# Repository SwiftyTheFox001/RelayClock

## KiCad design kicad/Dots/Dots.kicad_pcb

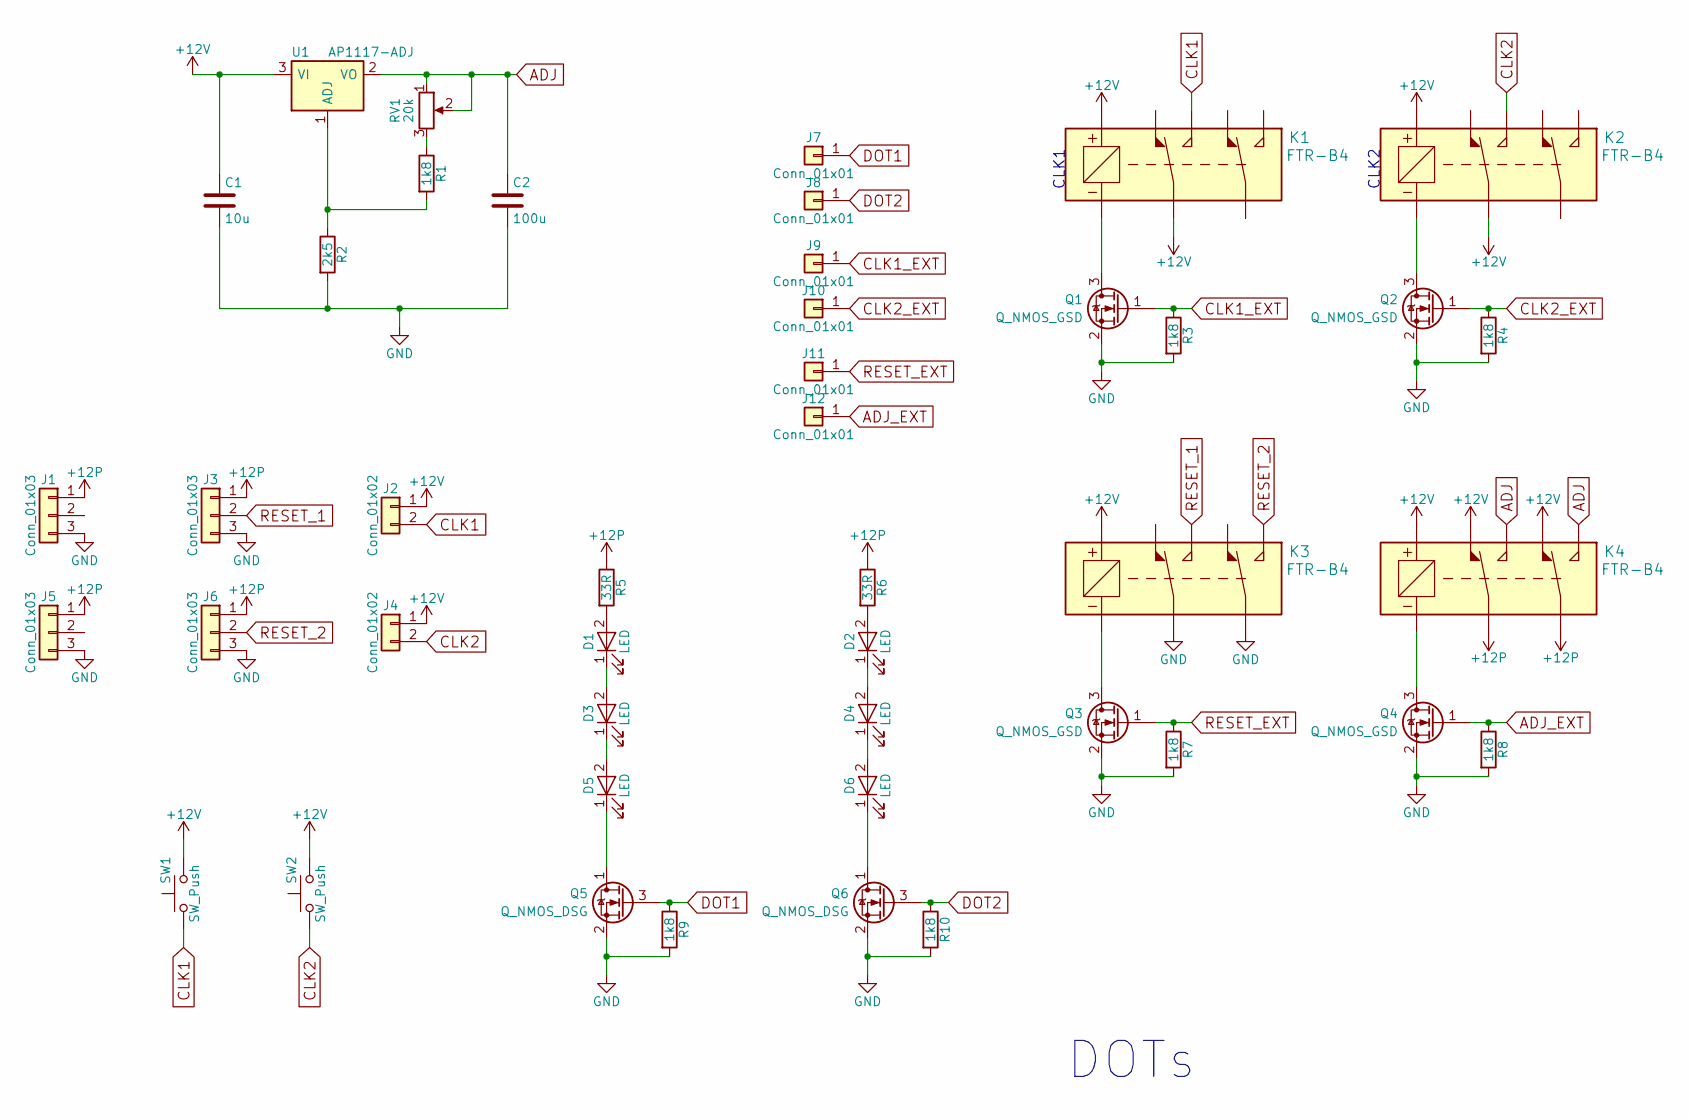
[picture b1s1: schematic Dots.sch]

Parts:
C1: 10u; C_Rect_L7.0mm_W3.5mm_P2.50mm_P5.00mm
C2: 100u; C_Rect_L7.0mm_W3.5mm_P2.50mm_P5.00mm
D1, D2, D3, D4, D5, D6: LED; LED_0805_2012Metric_Pad0.97x1.50mm_HandSolder
J1, J3, J5, J6: Conn_01x03; PinHeader_1x03_P2.54mm_Vertical
J2, J4: Conn_01x02; PinHeader_1x02_P2.54mm_Vertical
J7, J8, J9, J10, J11, J12: Conn_01x01; TestPoint_Pad_3.0x3.0mm
K1, K2, K3, K4: FTR-B4; FTR-B4_PTH
Q1, Q2, Q3, Q4: Q_NMOS_GSD; SOT-23
Q5, Q6: Q_NMOS_DSG; SOT-23
R1, R3, R4, R7, R8, R9, R10: 1k8; R_Axial_DIN0207_L6.3mm_D2.5mm_P10.16mm_Horizontal
R2: 2k5; R_Axial_DIN0207_L6.3mm_D2.5mm_P10.16mm_Horizontal
R5, R6: 33R; R_Axial_DIN0207_L6.3mm_D2.5mm_P10.16mm_Horizontal
RV1: 20k; TrimmPoti_Model23A_SMD
SW1, SW2: SW_Push; SW_PUSH_6mm
U1: AP1117-ADJ; SOT-223-3_TabPin2

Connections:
+12P: J1.1, J3.1, J5.1, J6.1, K4.3 (B2), K4.6 (A2), R5.1, R6.1
+12V: C1.1, J2.1, J4.1, K1.1 (+), K1.6 (A2), K2.1 (+), K2.6 (A2), K3.1 (+), K4.1 (+), K4.2 (B1), K4.7 (A1), SW1.2, SW2.2, U1.3 (VI)
ADJ: C2.1, K4.4 (B3), K4.5 (A3), RV1.1, RV1.2, U1.2 (VO)
ADJ_EXT: J12.1, Q4.1 (G), R8.1
CLK1: J2.2, K1.5 (A3), SW1.1
CLK1_EXT: J9.1, Q1.1 (G), R3.1
CLK2: J4.2, K2.5 (A3), SW2.1
CLK2_EXT: J10.1, Q2.1 (G), R4.1
DOT1: J7.1, Q5.3 (G), R9.1
DOT2: J8.1, Q6.3 (G), R10.1
GND: C1.2, C2.2, J1.3, J3.3, J5.3, J6.3, K3.3 (B2), K3.6 (A2), Q1.2 (S), Q2.2 (S), Q3.2 (S), Q4.2 (S), Q5.2 (S), Q6.2 (S), R2.2, R3.2, R4.2, R7.2, R8.2, R9.2, R10.2
unnamed: D1.1 (K), D3.2 (A)
unnamed: D1.2 (A), R5.2
unnamed: D2.1 (K), D4.2 (A)
unnamed: D2.2 (A), R6.2
unnamed: D3.1 (K), D5.2 (A)
unnamed: D4.1 (K), D6.2 (A)
unnamed: D5.1 (K), Q5.1 (D)
unnamed: D6.1 (K), Q6.1 (D)
unnamed: K1.8 (-), Q1.3 (D)
unnamed: K2.8 (-), Q2.3 (D)
unnamed: K3.8 (-), Q3.3 (D)
unnamed: K4.8 (-), Q4.3 (D)
unnamed: R1.1, RV1.3
unnamed: R1.2, R2.1, U1.1 (ADJ)
RESET_1: J3.2, K3.5 (A3)
RESET_2: J6.2, K3.4 (B3)
RESET_EXT: J11.1, Q3.1 (G), R7.1

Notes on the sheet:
CLK1
CLK2
DOTs

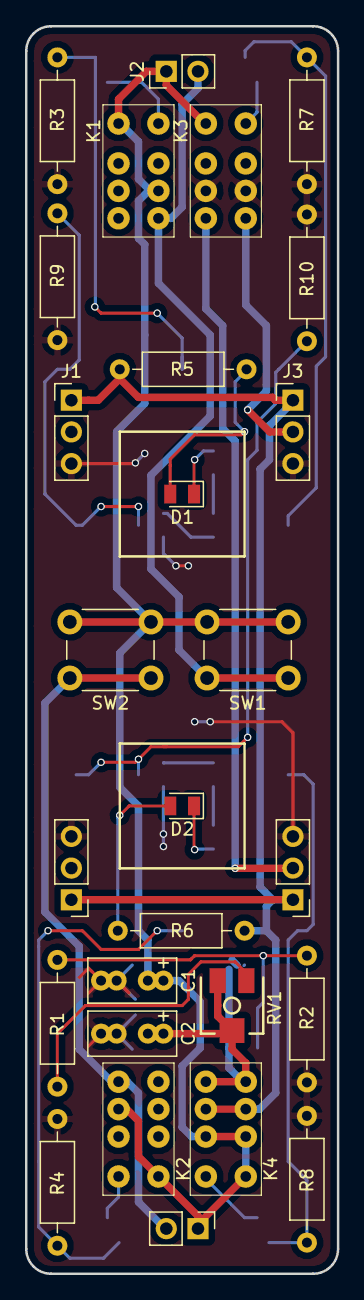
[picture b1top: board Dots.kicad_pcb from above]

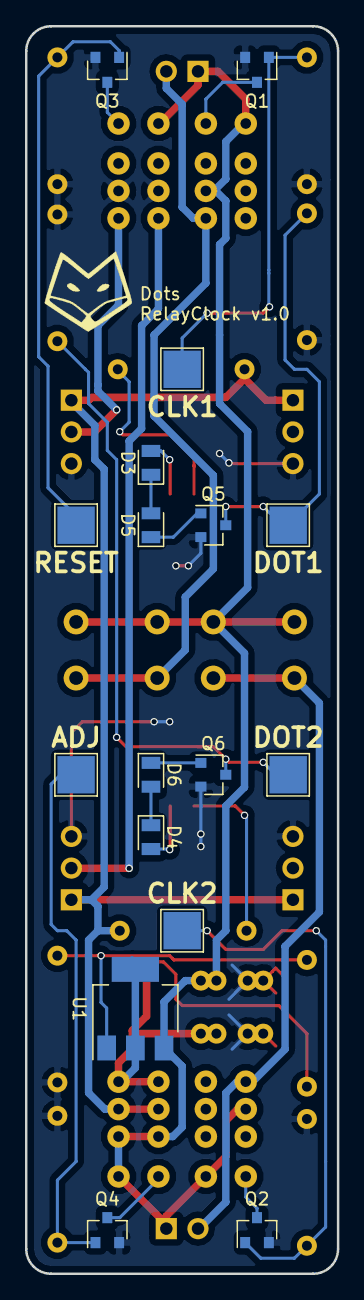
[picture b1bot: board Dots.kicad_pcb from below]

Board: 2 copper layers, 25.0 x 100.0 mm, 44 parts (17 on the bottom side), 28 nets.

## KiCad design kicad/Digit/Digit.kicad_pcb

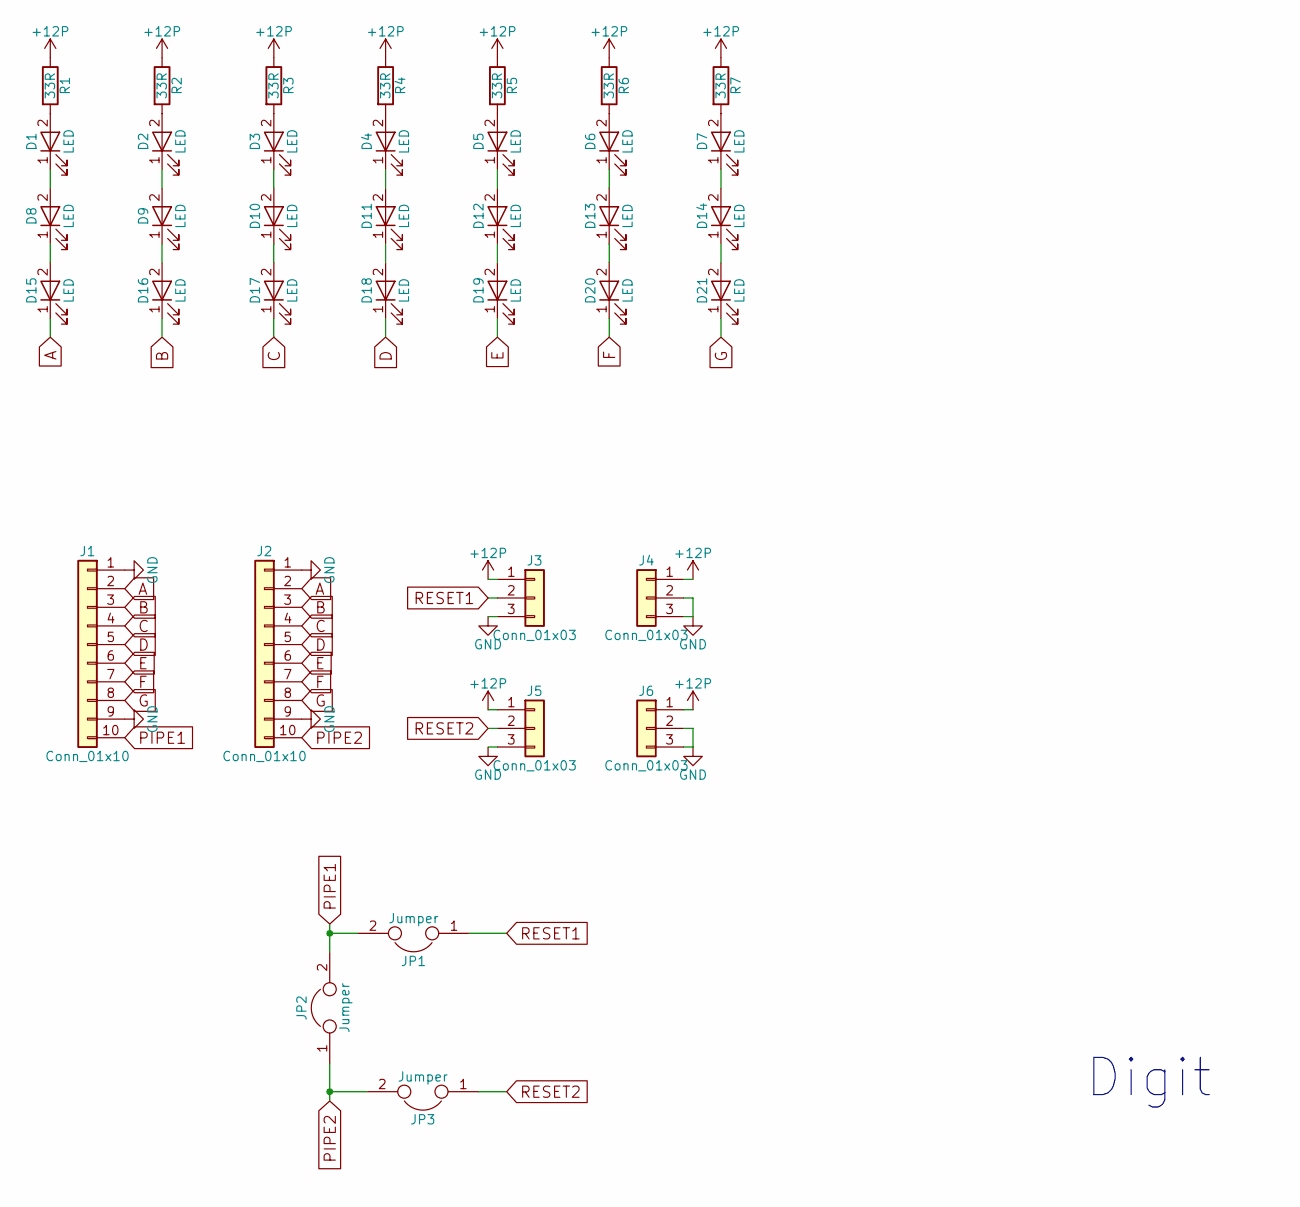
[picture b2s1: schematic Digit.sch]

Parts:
D1, D2, D3, D4, D5, D6, D7, D8, D9, D10, D11, D12, D13, D14, D15, D16, D17, D18, D19, D20, D21: LED; D_0805_2012Metric_Pad0.97x1.50mm_HandSolder
J1, J2: Conn_01x10; PinHeader_1x10_P2.54mm_Vertical
J3, J4, J5, J6: Conn_01x03; PinHeader_1x03_P2.54mm_Vertical
JP1, JP2, JP3: Jumper; SolderJumper_01x02
R1, R2, R3, R4, R5, R6, R7: 33R; R_Axial_DIN0207_L6.3mm_D2.5mm_P10.16mm_Horizontal

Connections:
+12P: J3.1, J4.1, J5.1, J6.1, R1.1, R2.1, R3.1, R4.1, R5.1, R6.1, R7.1
A: D15.1 (K), J1.2, J2.2
B: D16.1 (K), J1.3, J2.3
C: D17.1 (K), J1.4, J2.4
D: D18.1 (K), J1.5, J2.5
E: D19.1 (K), J1.6, J2.6
F: D20.1 (K), J1.7, J2.7
G: D21.1 (K), J1.8, J2.8
GND: J1.1, J1.9, J2.1, J2.9, J3.3, J4.2, J4.3, J5.3, J6.2, J6.3
unnamed: D1.1 (K), D8.2 (A)
unnamed: D1.2 (A), R1.2
unnamed: D2.1 (K), D9.2 (A)
unnamed: D2.2 (A), R2.2
unnamed: D3.2 (A), R3.2
unnamed: D4.2 (A), R4.2
unnamed: D5.2 (A), R5.2
unnamed: D6.2 (A), R6.2
unnamed: D7.2 (A), R7.2
unnamed: D10.1 (K), D17.2 (A)
unnamed: D3.1 (K), D10.2 (A)
unnamed: D11.1 (K), D18.2 (A)
unnamed: D4.1 (K), D11.2 (A)
unnamed: D12.1 (K), D19.2 (A)
unnamed: D5.1 (K), D12.2 (A)
unnamed: D13.1 (K), D20.2 (A)
unnamed: D6.1 (K), D13.2 (A)
unnamed: D14.1 (K), D21.2 (A)
unnamed: D7.1 (K), D14.2 (A)
unnamed: D8.1 (K), D15.2 (A)
unnamed: D9.1 (K), D16.2 (A)
PIPE1: J1.10, JP1.2, JP2.2
PIPE2: J2.10, JP2.1, JP3.2
RESET1: J3.2, JP1.1
RESET2: J5.2, JP3.1

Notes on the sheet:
Digit

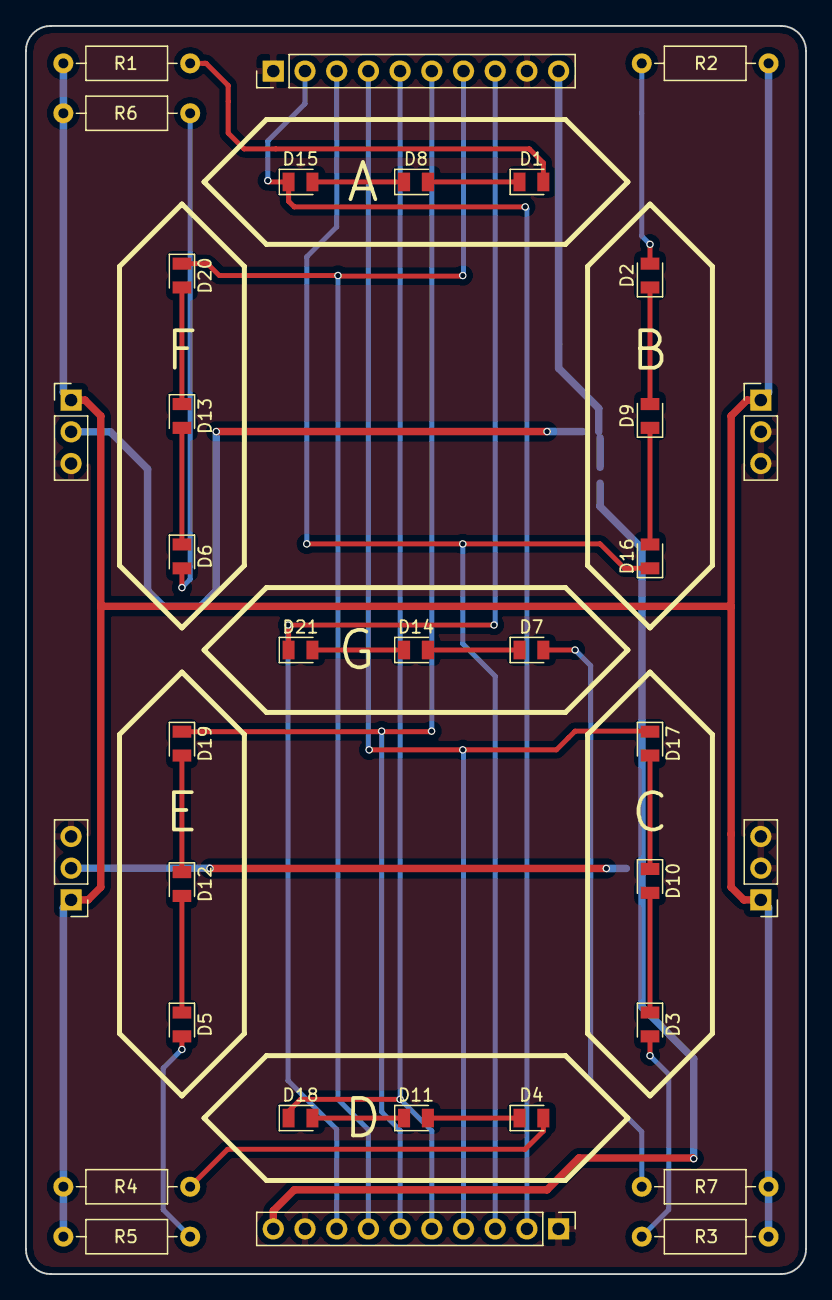
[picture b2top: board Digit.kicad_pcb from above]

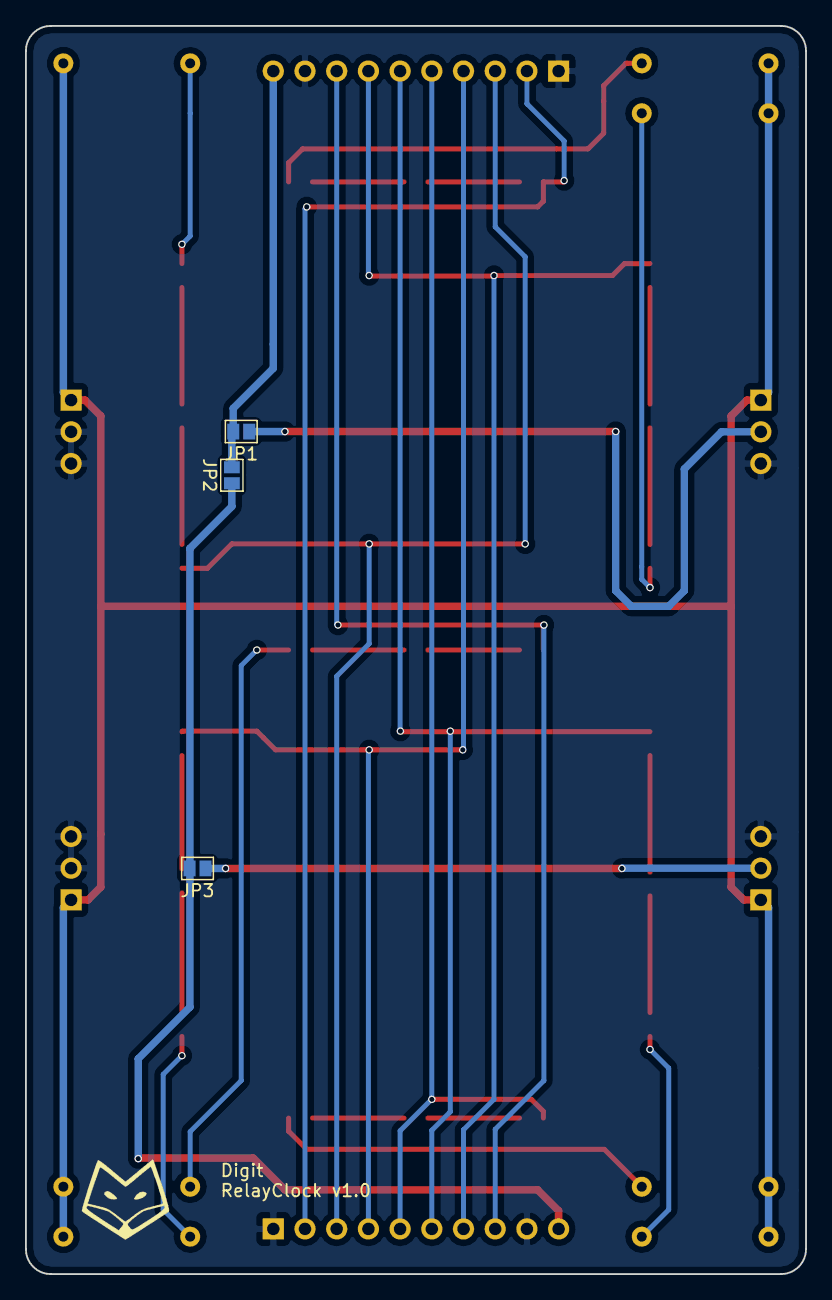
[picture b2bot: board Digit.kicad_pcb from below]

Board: 2 copper layers, 62.5 x 100.0 mm, 37 parts (3 on the bottom side), 34 nets.

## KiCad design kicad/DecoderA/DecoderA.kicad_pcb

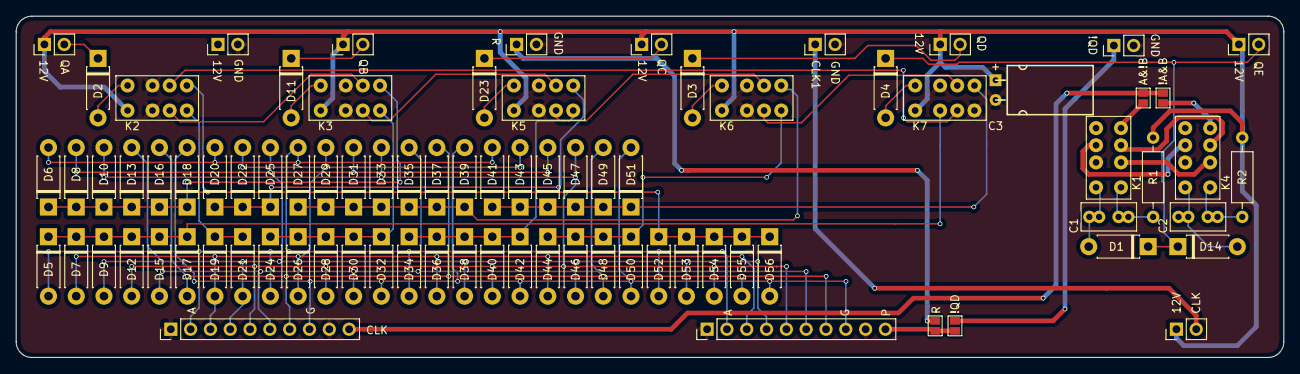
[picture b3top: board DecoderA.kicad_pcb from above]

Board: 2 copper layers, 162.5 x 43.8 mm, 84 parts (0 on the bottom side), 48 nets.

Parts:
C1, C2: CP; C_Rect_L7.0mm_W3.5mm_P2.50mm_P5.00mm
C3: CP; CP_Radial_D6.3mm_P2.50mm_W11.00mm_vertical
D1, D2, D3, D4, D5, D6, D7, D8, D9, D10, D11, D12, D13, D14, D15, D16, D17, D18, D19, D20, D21, D22, D23, D24, D25, D26, D27, D28, D29, D30, D31, D32, D33, D34, D35, D36, D37, D38, D39, D40, D41, D42, D43, D44, D45, D46, D47, D48, D49, D50, D51, D52, D53, D54, D55, D56: D; D_DO-41_SOD81_P7.62mm_Horizontal
J1, J2, J3, J4, J5, J6, J7, J10, J11, J12: Conn_01x02; PinHeader_1x02_P2.54mm_Vertical
J8, J9: Conn_01x10; PinHeader_1x10_P2.54mm_Vertical
JP1, JP2, JP3, JP4: Jumper; SolderJumper_01x02
K1, K2, K3, K4, K5, K6, K7: FTR-B4; FTR-B4_PTH
R1, R2: 100R; R_Axial_DIN0207_L6.3mm_D2.5mm_P10.16mm_Horizontal

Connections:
!A&B_POS: JP2.1, K4.4
!QD: J12.1, JP4.1
+12V: C3.1, J1.1, J2.1, J3.1, J4.1, J10.1, J11.1, K2.1, K3.1, K5.1, K6.1, K7.1, R1.1, R2.1
A: D5.2, D6.2, D20.2, D24.2, D27.2, D34.2, D41.2, D52.2, J8.2, J9.2
A&!B_POS: JP1.1, K1.4
B: D7.2, D19.2, D22.2, D26.2, D29.2, D36.2, D43.2, D44.2, J8.3, J9.3
C: D8.2, D9.2, D21.2, D25.2, D31.2, D38.2, D45.2, D46.2, D53.2, J8.4, J9.4
CLK1: J7.1, J11.2
CLK2: J9.10, JP1.2, JP2.2
D: D10.2, D12.2, D28.2, D33.2, D40.2, D47.2, D54.2, J8.5, J9.5
E: D13.2, D15.2, D30.2, D35.2, J8.6, J9.6
F: D16.2, D17.2, D37.2, D48.2, D49.2, D55.2, J8.7, J9.7
G: D18.2, D32.2, D39.2, D42.2, D50.2, D51.2, D56.2, J8.8, J9.8
GND: C3.2, J5.2, J6.2, J7.2, J8.1, J8.9, J9.1, J9.9, J12.2, K1.7, K2.2, K2.7, K3.2, K3.7, K4.7, K5.2, K5.7, K6.2, K6.7, K7.4, K7.7
NUM0: D5.1, D7.1, D9.1, D12.1, D15.1, D17.1, K7.2
NUM1: D19.1, D21.1, K2.4
NUM2: D24.1, D26.1, D28.1, D30.1, D32.1, K3.4
NUM3: D34.1, D36.1, D38.1, D40.1, D42.1, K5.4
NUM4: D44.1, D46.1, D48.1, D50.1, K6.4
NUM5: D52.1, D53.1, D54.1, D55.1, D56.1, K2.5
NUM6: D6.1, D8.1, D10.1, D13.1, D16.1, D18.1, K3.5
NUM7: D20.1, D22.1, D25.1, K5.5
NUM8: D27.1, D29.1, D31.1, D33.1, D35.1, D37.1, D39.1, K6.5
NUM9: D41.1, D43.1, D45.1, D47.1, D49.1, D51.1, K7.5
unnamed: C1.1, K1.1, R1.2
unnamed: C1.2, D1.2, K1.8
unnamed: C2.1, K4.1, R2.2
unnamed: C2.2, D14.2, K4.8
unnamed: D2.2, K2.8
unnamed: D3.2, K6.8
unnamed: D4.2, K7.8
unnamed: D11.2, K3.8
unnamed: D23.2, K5.8
unnamed: K1.2, K4.2
unnamed: K1.3, K4.3
unnamed: K1.6, K4.6
unnamed: K2.3, K3.6
unnamed: K2.6, K7.3
unnamed: K3.3, K5.6
unnamed: K5.3, K6.6
unnamed: K6.3, K7.6
PIPE: J8.10, JP3.2, JP4.2
QA: D2.1, J1.2
QB: D11.1, J2.2
QC: D23.1, J3.2
QD: D3.1, J4.2
QE: D1.1, D4.1, D14.1, J10.2
RESET: J6.1, JP3.1

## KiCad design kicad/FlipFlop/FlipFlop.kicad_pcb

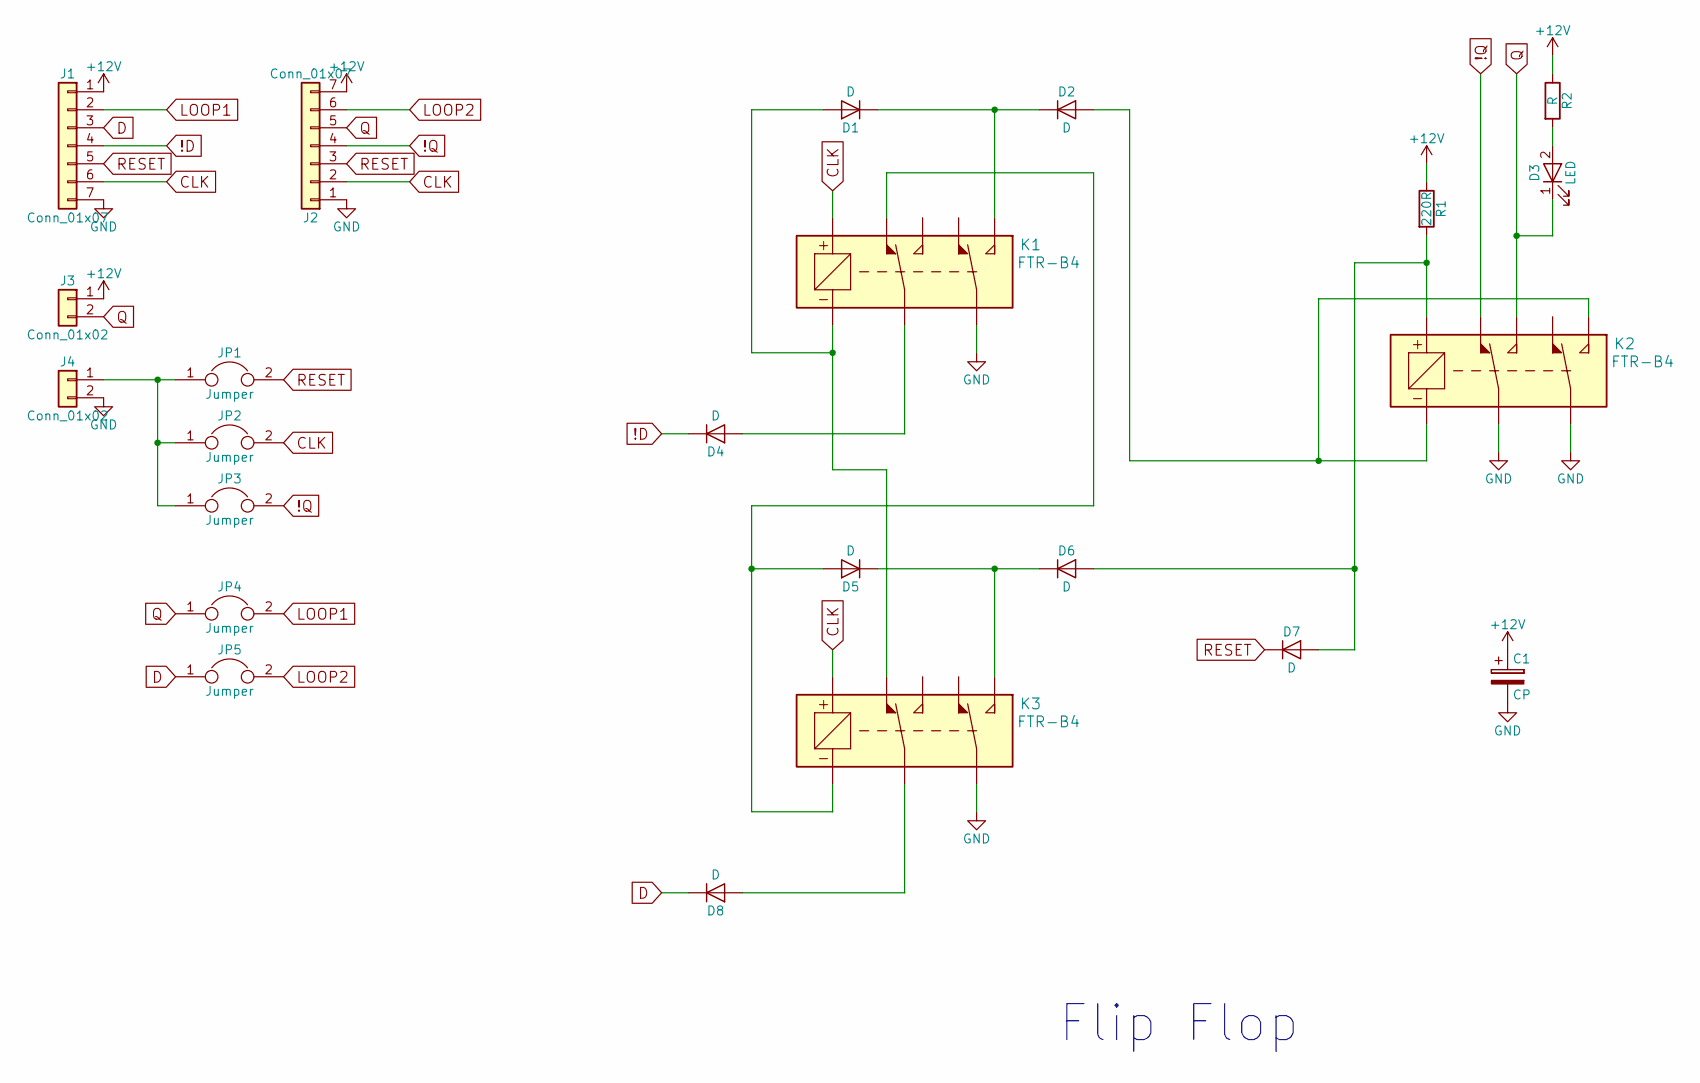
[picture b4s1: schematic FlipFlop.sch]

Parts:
C1: CP; CP_Radial_D6.3mm_P2.50mm_W11.00mm_vertical
D1, D2, D5, D6: D; D_DO-41_SOD81_P7.62mm_Horizontal
D3: LED; LED_0805_2012Metric_Pad0.97x1.50mm_HandSolder
D4, D7, D8: D; D_DO-41_SOD81_P2.54mm_Vertical_AnodeUp
J1, J2: Conn_01x07; PinHeader_1x07_P2.54mm_Vertical
J3, J4: Conn_01x02; PinHeader_1x02_P2.54mm_Vertical
JP1, JP2, JP3, JP4, JP5: Jumper; SolderJumper_01x02
K1, K2, K3: FTR-B4; FTR-B4_PTH
R1: 220R; R_Axial_DIN0207_L6.3mm_D2.5mm_P10.16mm_Horizontal
R2: R; R_Axial_DIN0207_L6.3mm_D2.5mm_P10.16mm_Horizontal

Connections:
!D: D4.1 (K), J1.4
!Q: J2.4, JP3.2, K2.7 (A1)
+12V: C1.1, J1.1, J2.7, J3.1, R1.1, R2.1
CLK: J1.6, J2.2, JP2.2, K1.1 (+), K3.1 (+)
D: D8.1 (K), J1.3, JP5.1
GND: C1.2, J1.7, J2.1, J4.2, K1.3 (B2), K2.3 (B2), K2.6 (A2), K3.3 (B2)
LOOP1: J1.2, JP4.2
LOOP2: J2.6, JP5.2
unnamed: D1.1 (K), D2.1 (K), K1.4 (B3)
unnamed: D1.2 (A), K1.8 (-), K3.7 (A1)
unnamed: D2.2 (A), K2.4 (B3), K2.8 (-)
unnamed: D3.2 (A), R2.2
unnamed: D4.2 (A), K1.6 (A2)
unnamed: D5.1 (K), D6.1 (K), K3.4 (B3)
unnamed: D5.2 (A), K1.7 (A1), K3.8 (-)
unnamed: D6.2 (A), D7.2 (A), K2.1 (+), R1.2
unnamed: D8.2 (A), K3.6 (A2)
unnamed: J4.1, JP1.1, JP2.1, JP3.1
Q: D3.1 (K), J2.5, J3.2, JP4.1, K2.5 (A3)
RESET: D7.1 (K), J1.5, J2.3, JP1.2

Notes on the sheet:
Flip Flop

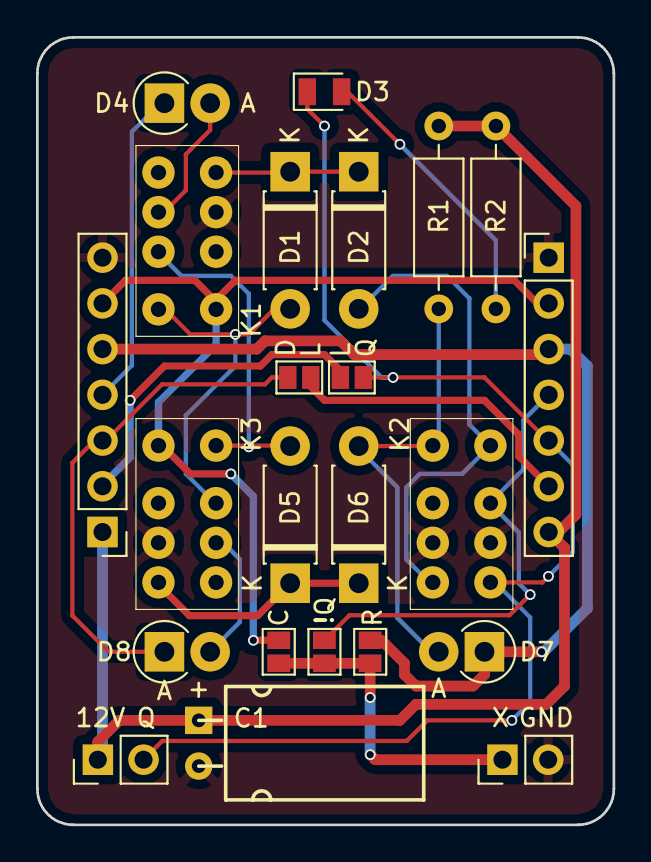
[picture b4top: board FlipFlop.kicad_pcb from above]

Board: 2 copper layers, 32.0 x 43.8 mm, 23 parts (0 on the bottom side), 20 nets.

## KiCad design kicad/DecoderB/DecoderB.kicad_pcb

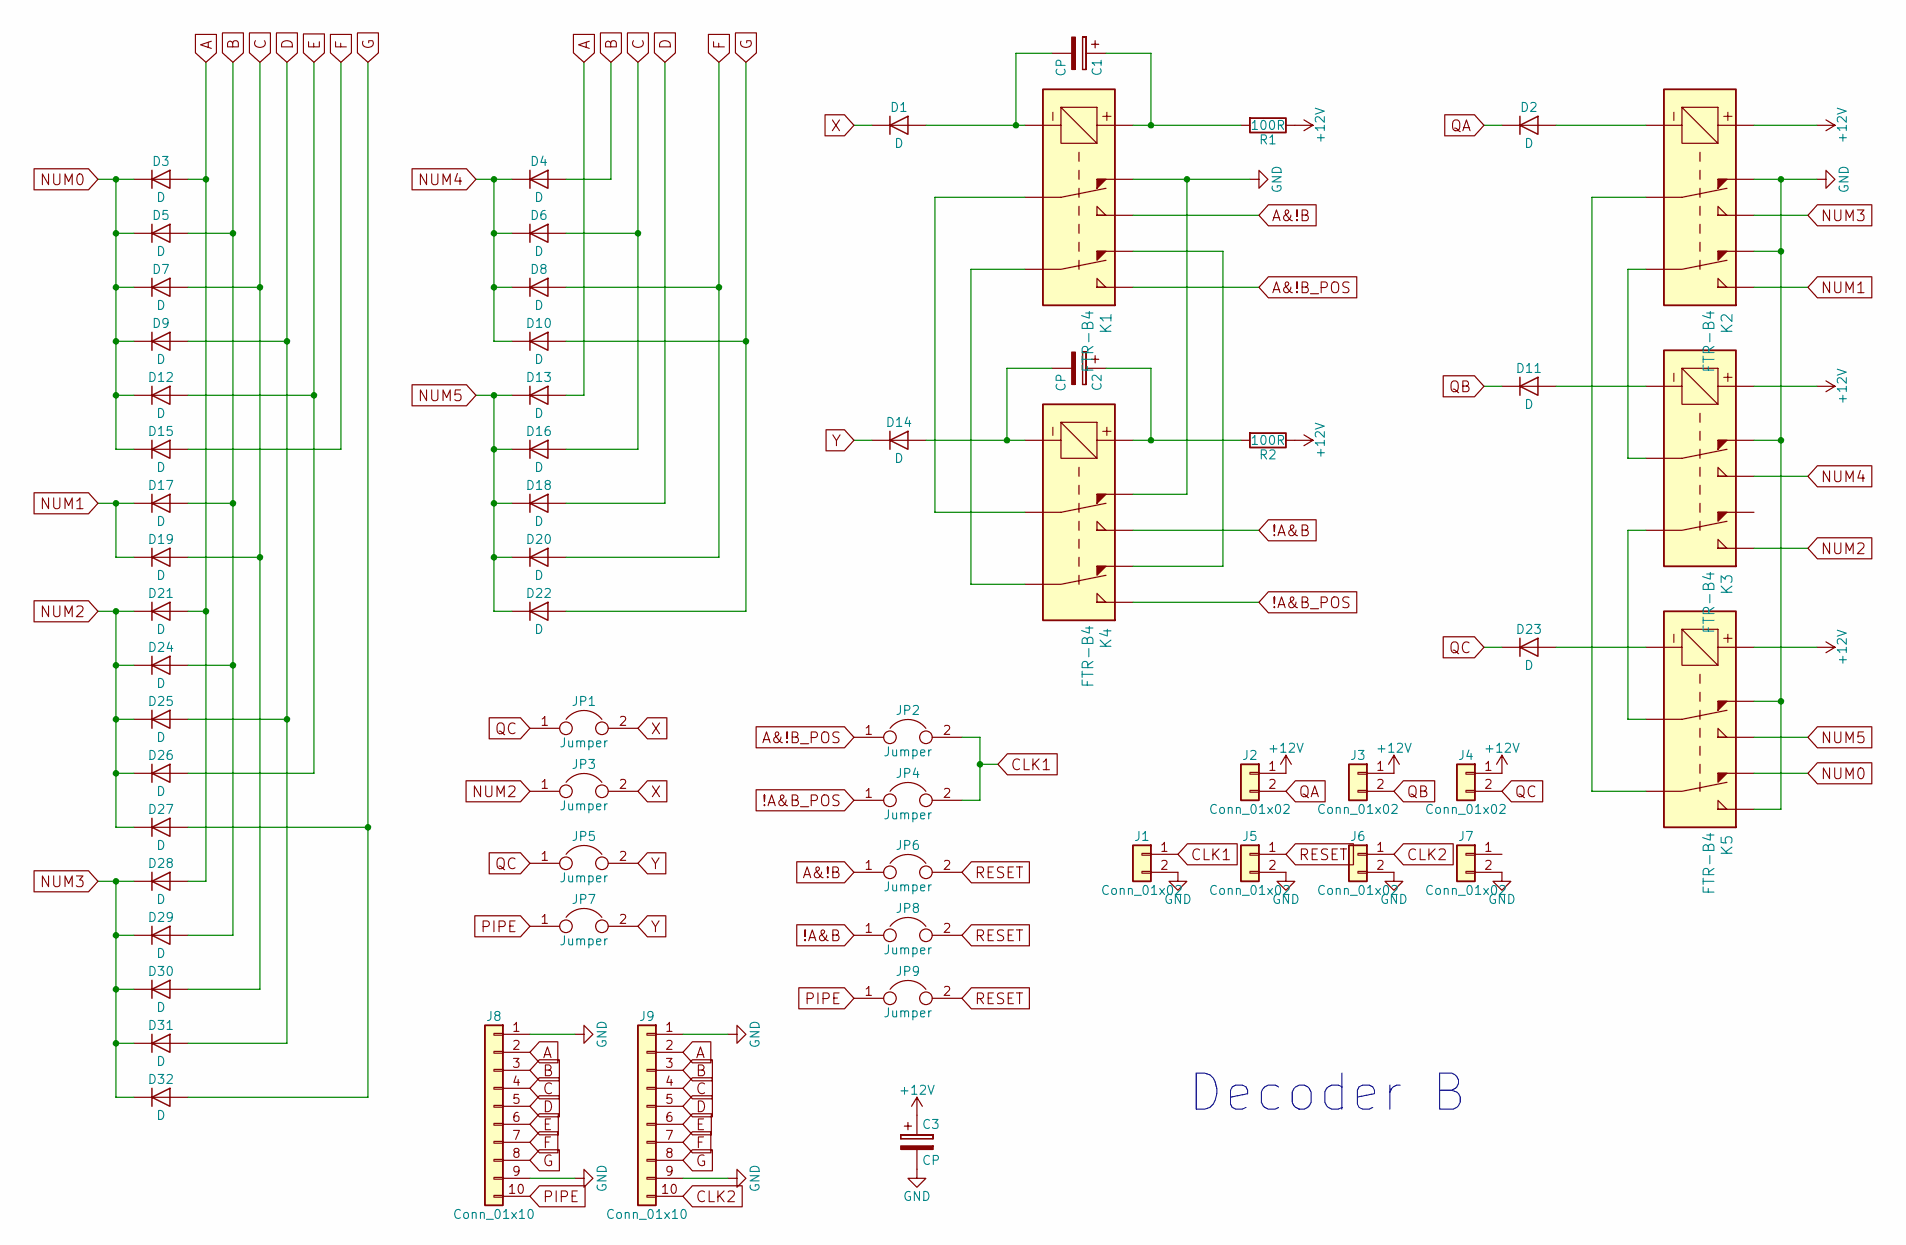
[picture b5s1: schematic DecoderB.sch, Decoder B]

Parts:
C1, C2: CP; C_Rect_L7.0mm_W3.5mm_P2.50mm_P5.00mm
C3: CP; CP_Radial_D6.3mm_P2.50mm_W11.00mm_vertical
D1, D2, D3, D4, D5, D6, D7, D8, D9, D10, D11, D12, D13, D14, D15, D16, D17, D18, D19, D20, D21, D22, D23, D24, D25, D26, D27, D28, D29, D30, D31, D32: D; D_DO-41_SOD81_P7.62mm_Horizontal
J1, J2, J3, J4, J5, J6, J7: Conn_01x02; PinHeader_1x02_P2.54mm_Vertical
J8, J9: Conn_01x10; PinHeader_1x10_P2.54mm_Vertical
JP1, JP2, JP3, JP4, JP5, JP6, JP7, JP8, JP9: Jumper; SolderJumper_01x02
K1, K2, K3, K4, K5: FTR-B4; FTR-B4_PTH
R1, R2: 100R; R_Axial_DIN0207_L6.3mm_D2.5mm_P10.16mm_Horizontal

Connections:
!A&B: JP8.1, K4.5 (A3)
!A&B_POS: JP4.1, K4.4 (B3)
+12V: C3.1, J2.1, J3.1, J4.1, K2.1 (+), K3.1 (+), K5.1 (+), R1.1, R2.1
A: D3.2 (A), D13.2 (A), D21.2 (A), D28.2 (A), J8.2, J9.2
A&!B: JP6.1, K1.5 (A3)
A&!B_POS: JP2.1, K1.4 (B3)
B: D4.2 (A), D5.2 (A), D17.2 (A), D24.2 (A), D29.2 (A), J8.3, J9.3
C: D6.2 (A), D7.2 (A), D16.2 (A), D19.2 (A), D30.2 (A), J8.4, J9.4
CLK1: J1.1, JP2.2, JP4.2
CLK2: J6.1, J9.10
D: D9.2 (A), D18.2 (A), D25.2 (A), D31.2 (A), J8.5, J9.5
E: D12.2 (A), D26.2 (A), J8.6, J9.6
F: D8.2 (A), D15.2 (A), D20.2 (A), J8.7, J9.7
G: D10.2 (A), D22.2 (A), D27.2 (A), D32.2 (A), J8.8, J9.8
GND: C3.2, J1.2, J5.2, J6.2, J7.2, J8.1, J8.9, J9.1, J9.9, K1.7 (A1), K2.2 (B1), K2.7 (A1), K3.7 (A1), K4.7 (A1), K5.4 (B3), K5.7 (A1)
NUM0: D3.1 (K), D5.1 (K), D7.1 (K), D9.1 (K), D12.1 (K), D15.1 (K), K5.2 (B1)
NUM1: D17.1 (K), D19.1 (K), K2.4 (B3)
NUM2: D21.1 (K), D24.1 (K), D25.1 (K), D26.1 (K), D27.1 (K), JP3.1, K3.4 (B3)
NUM3: D28.1 (K), D29.1 (K), D30.1 (K), D31.1 (K), D32.1 (K), K2.5 (A3)
NUM4: D4.1 (K), D6.1 (K), D8.1 (K), D10.1 (K), K3.5 (A3)
NUM5: D13.1 (K), D16.1 (K), D18.1 (K), D20.1 (K), D22.1 (K), K5.5 (A3)
unnamed: C1.1, K1.1 (+), R1.2
unnamed: C1.2, D1.2 (A), K1.8 (-)
unnamed: C2.1, K4.1 (+), R2.2
unnamed: C2.2, D14.2 (A), K4.8 (-)
unnamed: D2.2 (A), K2.8 (-)
unnamed: D11.2 (A), K3.8 (-)
unnamed: D23.2 (A), K5.8 (-)
unnamed: K1.2 (B1), K4.2 (B1)
unnamed: K1.3 (B2), K4.3 (B2)
unnamed: K1.6 (A2), K4.6 (A2)
unnamed: K2.3 (B2), K3.6 (A2)
unnamed: K2.6 (A2), K5.3 (B2)
unnamed: K3.3 (B2), K5.6 (A2)
PIPE: J8.10, JP7.1, JP9.1
QA: D2.1 (K), J2.2
QB: D11.1 (K), J3.2
QC: D23.1 (K), J4.2, JP1.1, JP5.1
RESET: J5.1, JP6.2, JP8.2, JP9.2
X: D1.1 (K), JP1.2, JP3.2
Y: D14.1 (K), JP5.2, JP7.2

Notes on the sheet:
Decoder B

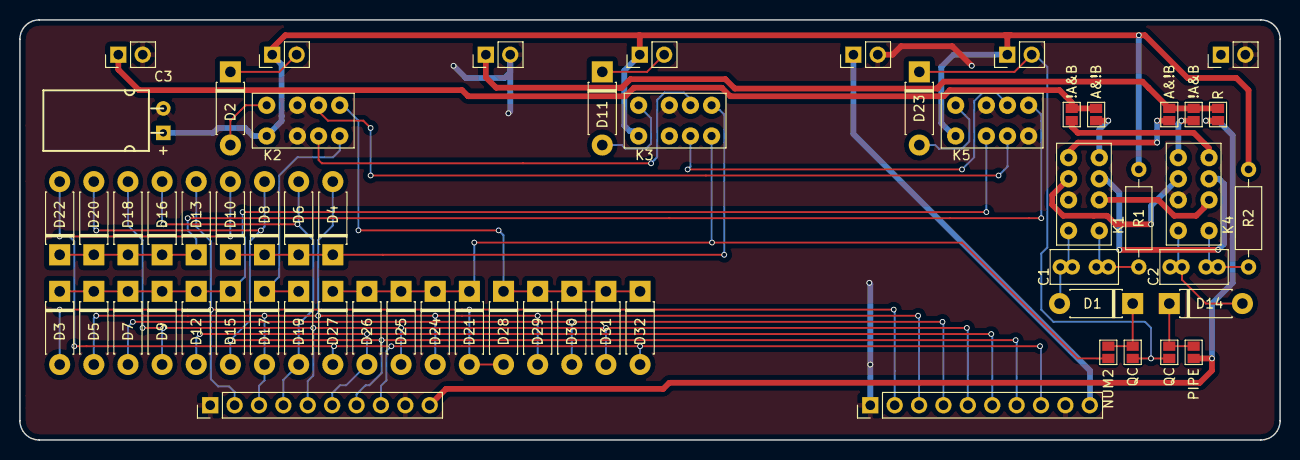
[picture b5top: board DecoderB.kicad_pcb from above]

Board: 2 copper layers, 131.2 x 43.8 mm, 60 parts (0 on the bottom side), 41 nets.

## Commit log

2018-02-17 first upload of all files from local folder
